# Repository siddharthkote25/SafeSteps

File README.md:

# SafeSteps — PCB Design

### 🚨 Personal Safety & Emergency Response Device

**SafeSteps** is my final-year B.Tech project: an electronics hardware design for a personal safety and emergency response device. The system uses an **ESP32, a GPS module and a 4G LTE module** to provide location tracking and emergency (SOS) communication, powered by a Li-Po battery.

This repository contains the **KiCad 9 schematic, PCB layout, custom symbols and footprints, DRC report and Gerber files** for the SafeSteps hardware.

---

## 🔧 Hardware

| Component                  | Purpose                                 |
| -------------------------- | --------------------------------------- |
| **ESP32**                  | Main microcontroller                    |
| **NEO-6M GPS**             | Location tracking                       |
| **A7670C 4G LTE**          | Cellular communication / SOS alerts     |
| **HT7333**                 | 3.3 V voltage regulation                |
| **Li-Po battery**          | Power source                            |
| **SOS button**             | Triggers the emergency alert            |
| **LED and buzzer**         | Status indication and audible alert     |
| **Resistors & Capacitors** | Signal conditioning and power filtering |
| **Connectors**             | Module and external connections         |

---

## 📐 Schematic Design

The circuit schematic was designed in **KiCad 9**, connecting the main controller, communication modules, power supply, and supporting components.

### SafeSteps Schematic

### Key Design Work

* Schematic capture and circuit connectivity
* Custom symbol creation and component symbol selection
* Net labeling
* Power and ground connections
* UART connections between ESP32, GPS and LTE module
* GPIO connections for the SOS button, LED and buzzer
* 3.3 V power regulation using HT7333
* Electrical Rules Check (ERC)

---

## 🖥️ PCB Design

The project follows a complete **KiCad PCB design workflow**:

```text
Schematic → Symbol & Footprint Assignment → ERC → PCB Layout
→ Component Placement → Net Classes & Design Rules → Routing → DRC → Gerbers
```

### PCB Layout

### 3D View

### PCB Design Work

* PCB layout and board organization
* Component placement
* Through-hole / SMD footprint management
* Custom footprint creation and integration
* Net classes, trace width and clearance configuration
* Power and signal routing
* Ground connections
* ERC troubleshooting and DRC validation
* Gerber and drill file generation (see `Gerbers/`)

---

## 🔌 Main Connections

```text
   Li-Po battery ──► HT7333 (3.3 V regulator) ──► board power

                    ┌──────────────┐
   SOS button ─────►│              │────► LED
                    │    ESP32     │
                    │     MCU      │────► Buzzer
                    └──────┬───────┘
                           │
                 ┌─────────┴─────────┐
               UART                UART
                 │                   │
          ┌──────▼──────┐     ┌──────▼──────┐
          │   NEO-6M    │     │   A7670C    │
          │     GPS     │     │   4G LTE    │
          └─────────────┘     └─────────────┘
```

---

## 🛠️ Tools & Technologies

**PCB Design**

* KiCad 9
* Schematic Capture
* PCB Layout
* Footprint and Symbol Creation
* Component Placement
* Routing
* ERC / DRC
* Net Classes and Design Rules
* Gerber Generation

**Electronics**

* ESP32
* GPS and 4G LTE modules
* Voltage Regulation
* UART and GPIO
* Power & Signal Routing

**Version Control**

* Git
* GitHub

---

## 📂 Repository Contents

```text
SafeSteps/
│
├── Foot-prints/                      # Custom footprints
├── symbols/                          # Custom symbols
├── Gerbers/                          # Manufacturing files
├── Safesteps.kicad_sch               # Schematic
├── Safesteps.kicad_pcb               # PCB layout
├── Safesteps.kicad_pro               # KiCad project file
├── DRC.rpt                           # Design Rule Check report
├── SafeSteps (Schematic design ).png # Schematic image
├── layout design (Safesteps.png      # PCB layout image
├── 3d view design.png                # 3D render
└── README.md
```

---

## 🎯 Skills Demonstrated

`KiCad 9` `PCB Design` `Schematic Capture` `PCB Layout`
`Custom Symbols & Footprints` `Component Placement` `Routing` `Net Classes`
`ERC` `DRC` `Gerber Generation` `UART` `Power Regulation` `Git` `GitHub`

---

### 👨‍💻 Author

**Siddharth Kote**
siddharthkote129@gmail.com

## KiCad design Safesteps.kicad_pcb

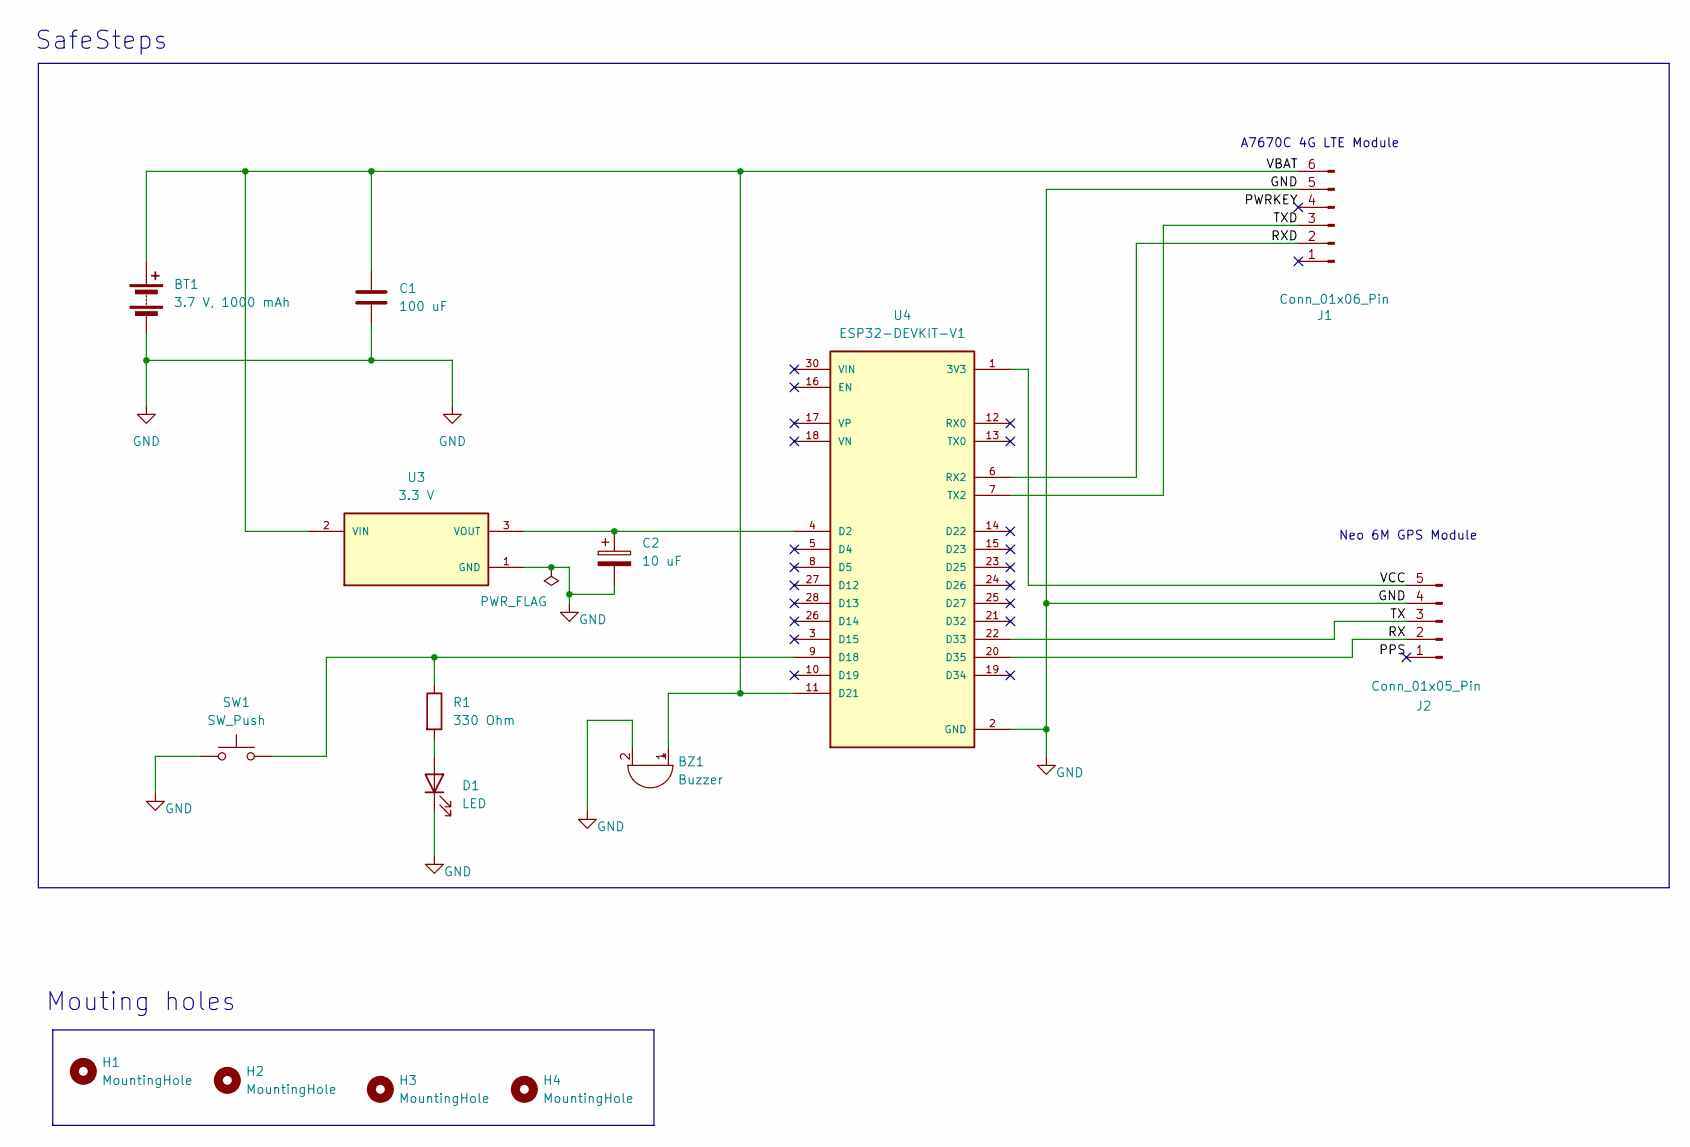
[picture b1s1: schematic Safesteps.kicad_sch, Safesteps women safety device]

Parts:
BT1: 3.7 V, 1000 mAh; JST_PH_B2B-PH-K_1x02_P2.00mm_Vertical
BZ1: Buzzer; Buzzer_15x7.5RM7.6
C1: 100 uF; C_0805_2012Metric
C2: 10 uF; C_0805_2012Metric
D1: LED; LED_D5.0mm
H1, H2, H3, H4: MountingHole; MountingHole_2.1mm
J1: Conn_01x06_Pin; PinHeader_1x06_P2.54mm_Vertical
J2: Conn_01x05_Pin; PinHeader_1x05_P2.54mm_Vertical
R1: 330 Ohm; R_0805_2012Metric
SW1: SW_Push; SW_PUSH-12mm
U3: 3.3 V; IC_HT7333; PARTREV 1.80
U4: ESP32-DEVKIT-V1; MODULE_ESP32_DEVKIT_V1; PARTREV N/A

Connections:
/PPS: J2.1
/PWRKEY: J1.4
/RF: J1.1
/RX: J2.2, U4.20 (D35)
/RXD: J1.2, U4.6 (RX2)
/TX: J2.3, U4.22 (D33)
/TXD: J1.3, U4.7 (TX2)
/VBAT: BT1.1 (+), BZ1.1 (+), C1.1, J1.6, U3.2 (VIN), U4.11 (D21)
/VCC: J2.5, U4.1 (3V3)
GND: BT1.2 (-), BZ1.2 (-), C1.2, C2.2, D1.1 (K), J1.5, J2.4, SW1.1, U3.1 (GND), U4.2 (GND), U4.29 (GND)
unnamed: D1.2 (A), R1.2
unnamed: C2.1, U3.3 (VOUT), U4.4 (D2)
unnamed: R1.1, SW1.2, U4.9 (D18)

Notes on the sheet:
SafeSteps
A7670C 4G LTE Module
Neo 6M GPS Module
Mouting holes

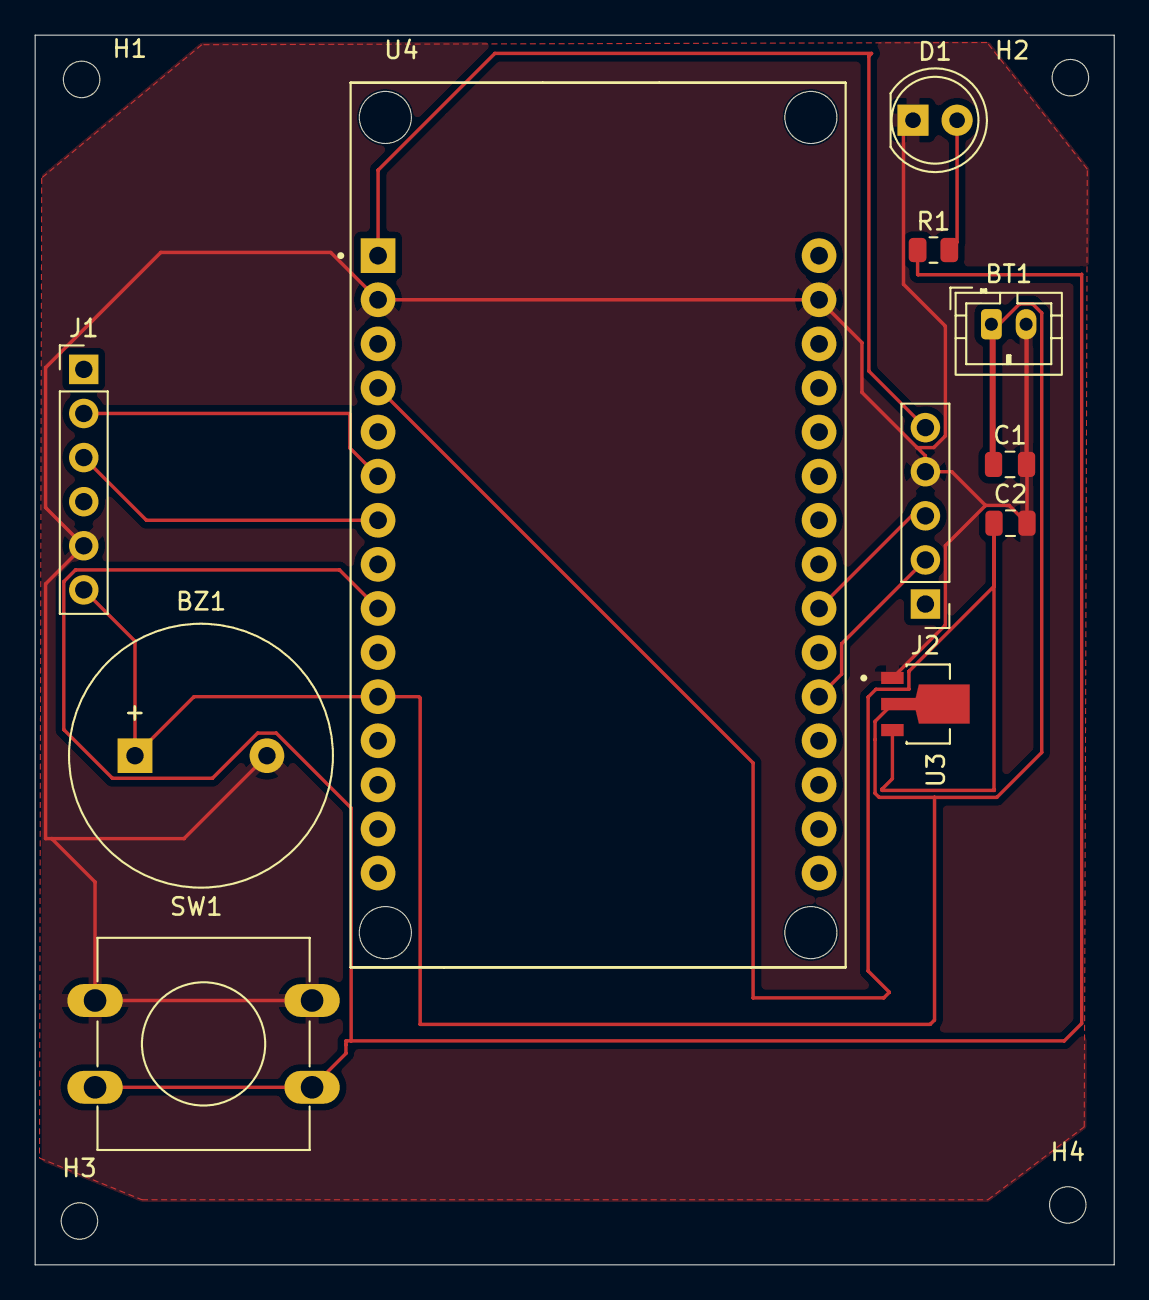
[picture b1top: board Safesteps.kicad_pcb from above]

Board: 2 copper layers, 62.2 x 70.8 mm, 15 parts (0 on the bottom side), 10 nets.
